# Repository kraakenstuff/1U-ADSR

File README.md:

# 1U-ADSR
1U Eurorack ADSR module based on René Schmitz' schematic (https://www.schmitzbits.de/adsr.html)

Status: kinda works. I think that pcb will not be changed any more, but values need to be changed

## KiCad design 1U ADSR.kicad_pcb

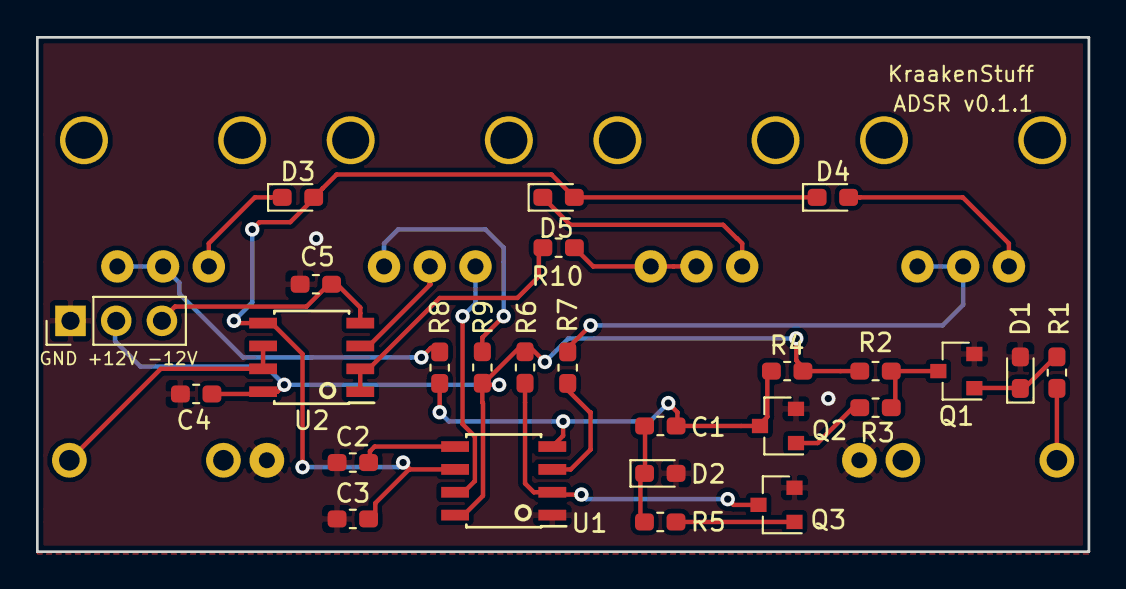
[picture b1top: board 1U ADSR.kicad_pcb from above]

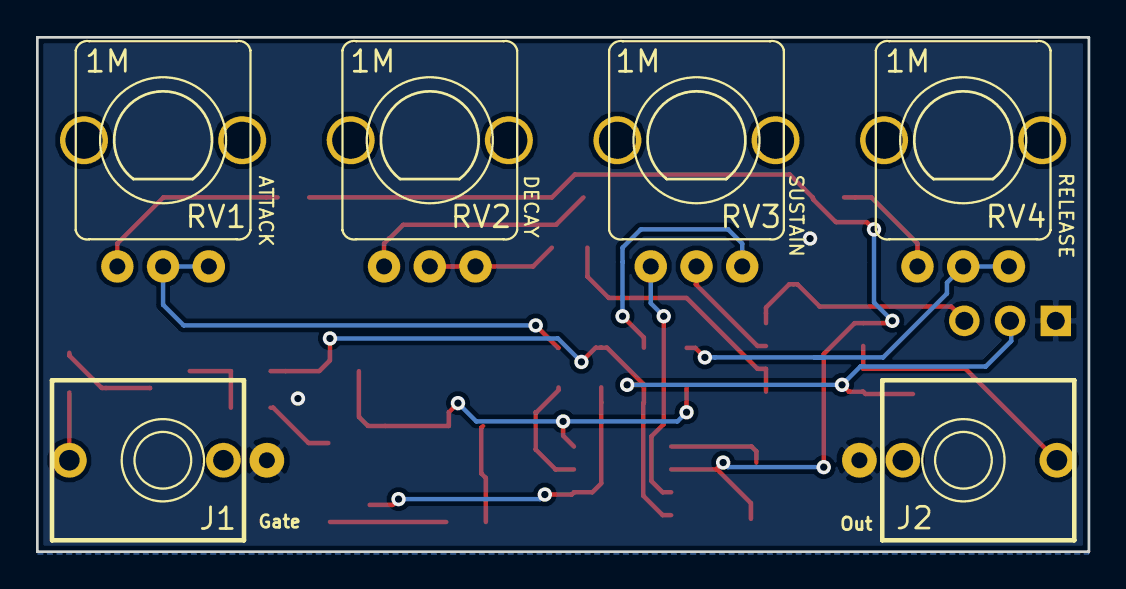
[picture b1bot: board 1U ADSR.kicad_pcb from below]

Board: 2 copper layers, 58.4 x 28.6 mm, 32 parts (6 on the bottom side), 25 nets.

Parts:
C1, C2: 10n; C_0603_1608Metric_Pad1.05x0.95mm_HandSolder
C3: 4u7; C_0603_1608Metric_Pad1.05x0.95mm_HandSolder
C4, C5: 100n; C_0603_1608Metric_Pad1.05x0.95mm_HandSolder
D1, D2, D3, D4, D5: 1n4148; D_0603_1608Metric_Pad1.05x0.95mm_HandSolder
GND +12V -12V: PWR; PinHeader_1x03_P2.54mm_Vertical
J1: Gate; PJ301M-12
J2: Out; PJ301M-12
Q1, Q2, Q3: BC847; SOT-23
R1, R5: 10k; R_0603_1608Metric_Pad1.05x0.95mm_HandSolder
R2, R4, R6, R9: 4k7; R_0603_1608Metric_Pad1.05x0.95mm_HandSolder
R3: 22k; R_0603_1608Metric_Pad1.05x0.95mm_HandSolder
R7, R8, R10: 100R; R_0603_1608Metric_Pad1.05x0.95mm_HandSolder
RV1, RV2, RV3, RV4: 1M; POT-9MM-ALPHA
U1: NE555; SOIC-8_3.9x4.9mm_P1.27mm
U2: LM358; SOIC-8_3.9x4.9mm_P1.27mm

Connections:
+12V: C4.2, GND +12V -12V.2, R2.2, R4.2, R6.2, R9.1, U1.8, U2.8
-12V: C5.1, GND +12V -12V.3, U2.4
GND: C2.1, C3.1, C4.1, C5.2, D1.2, D2.2, GND +12V -12V.1, J1.S, J2.S, Q1.2, Q2.2, Q3.2, U1.1
unnamed: C1.1, D2.1, R5.2
unnamed: C1.2, Q2.3, R4.1, R8.2, U1.4
unnamed: C2.2, U1.5
unnamed: C3.2, D3.2, D4.1, D5.2, U1.6, U2.5
unnamed: D1.1, Q1.1, R1.1
unnamed: D3.1, RV4.1
unnamed: D4.2, RV1.1
unnamed: D5.1, RV2.1
unnamed: J1.T, R1.2
unnamed: J2.T, U2.6, U2.7
unnamed: Q1.3, R2.1, R3.2
unnamed: Q2.1, R3.1
unnamed: Q3.1, R5.1
unnamed: Q3.3, R6.1, U1.2
unnamed: R7.1, RV1.2, RV1.3
unnamed: R7.2, U1.3
unnamed: R8.1, RV4.2, RV4.3
unnamed: R9.2, RV3.3
unnamed: R10.1, U2.1, U2.2
unnamed: R10.2, RV2.2, RV2.3
unnamed: RV3.1, U1.7
unnamed: RV3.2, U2.3

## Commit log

2018-11-25 removed backup file
2018-11-25 added .gitignore
2018-11-25 Changed gitignore to the standard one
2019-01-07 Updated schematic with new KiCad symbols
2019-01-07 Finished v0.1
2019-01-21 Fixed potentiometers orientation.
2019-01-22 Changed the version on pcb
2019-02-13 Minor refactoring of schematic
